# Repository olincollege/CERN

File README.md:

# CERN
ENGR 2110 Final Project: Centripetal Electronic Robotic Navigator (CERN)

#### Final Project by Ari Bobesh (Electrical), Venkadesh Eswaranandam (Electrical), Angela Huang (Mechancial), Sohum Kothavade (Mechanical), and Kevin Lie-Atjam (Firmware/Software)

Welcome to the Centripetal Electronic Robotic Navigator (CERN) project! In this repository, we embark on our exciting journey to build our own version of a Sphero-like robot—a small, spherical robot capable of dynamic movements and engaging interactions. Our goal was to create a Sphero-like robot with inductive charging, a custom PCB, modular and elegant design, and coherent software to control the robot.

## Dependencies and Repository Overview
This software runs on both C++ and Python. Our C++ infrastructure includes firmware for an ESP32 that can run the robot's control algorithms to drive the robot. The Python infrasture include code that is required to connect to the ESP32 over Bluetooth serial to control the robot.

## Repository Structure
The repository has a set of 4 folders which each have important information regarding the items inside of the repository

### app_interface
`app_interface` contains the Python script file required to run our control interface for our robots

### kicad
`kicad` contains a set of schematics and PCB board designs utilized in our project. Inside this folder, the `kicad.kicad_sch` file contains the transmitting circuit for the inductive charging base station. `robot.kicad_sch` and `robot.kicad_pcb` contain the circuit and PCB respectively for the receiving end of the charging circuit and the control circuitry placed inside our robot.

### motor_communicate
`motor_communicate` contains the C++ firmware required to run the robot.

### SymFoot
`SymFoot` contains footprints and symbols for our schematic with unique components not readily available in KiCAD.

### Library installation and Dependencies
To run the software, you will need the following:
* A Unix/Linux Operating System
* A Python Environment (Ex. Anaconda)
* PySerial
* Pygame
* PyBluez

To install the all of the necessary libraries, we recommend doing the following:
* Ensure that you're running a version of Python that is 3.9 or above
* Open a bash terminal on your machine
* Once it loads, I recommend creating a new Anaconda environment. This can be done by doing the following
```
conda create --name <Environment Name> python=3.9
```
Where you may name your environment whatever you would like
* Be patient and make sure that you type y to create your environment after a dialog box appears
* After the environment has been created, run the following command
```
conda activate <Environment Name>
```
To activate your Anaconda environment
* You're now ready to install the libraries to use this repository. Ensure that your file directory is at the root of this repository. By typing `ls` in the repository directory, you should see a file called `requirements.txt`. Finally, you can run the following

```
pip install -r requirements.txt
```
* Be patient and wait for the libraries to finish installing

## Robot Information
We built a set of 3 CERN Robots. The connection information and motor pinouts have been provided

| Name | MAC Address | Drive Pins | Turn Pins |
| ------- | ----- | ----- | ----- |
| Stubby | 78:21:84:B9:0A:1E | A1A: 33<br /> A1B: 32<br /> B1A: 2<br /> B1B: 23<br /> Sleep: 25| A1A: 12<br /> A1B: 14<br /> B1A: 26<br /> B1B: 27<br /> Sleep: 13|
| Girthy | E0:5A:1B:E4:66:56 | A1A: 26<br /> A1B: 27<br /> B1A: 14<br /> B1B: 12<br /> Sleep: 13| A1A: 2<br /> A1B: 23<br /> B1A: 32<br /> B1B: 33<br /> Sleep: 25
| Kirby | E0:5A:1B:E4:9D:D6 | A1A: 32<br /> A1B: 33<br /> B1A: 2<br /> B1B: 23<br /> Sleep: 25| A1A: 12<br /> A1B: 14<br /> B1A: 27<br /> B1B: 26<br /> Sleep: 13

## Connecting To The Robot

These steps work best with Linux based systems

Firstly, make sure that the robot you want to connect to is on. Next, you'll want to connect to the robot by Bluetooth using the systems settings to connect to your robot. You will briefly connect to the robot, but you will then disconnect to the robot. This doesn't mean that you've lost connection, but this only means that you've placed the connection to the robot as a familiar device. Next, you're going to want to run friendly_control.py under the app_interface folder which can be executed by using the following command in a bash terminal: `python friendly_control.py` which will then ask you what device you would like to connect to. You may also open the Python script in a code editor and run the code manually. Once you run the code, it will then ask you to enter your password to because the controls will enter in root. This is because the following code is ran `sudo rfcomm bind <PORT NUMBER> <MAC ADDRESS>` which is when a radio frequency communication port will be established by your computer and robot to the Bluetooth MAC address of your robot. This is important since data is sent over serial for bluetooth. This then opens up a Pygame experience which should allow you obtain live data of the robot, control the lights of the robot, and control the robot using the WASD keys. Once you've finished driving the robot, you may close the Pygame interface, and the following command is ran: `sudo rfcomm release <PORT NUMBER>` which is when the communication port established will be dissolved, and the robot can then be reconnected or connected to another client.

If you have trouble connecting to the robot, typically running `sudo rfcomm release <PORT NUMBER>` to ensure that there doesn't exist a port that already exists that the robot tries to talk to on your computer to is typically recommended.

If you have any questions about any aspect about our project, please feel free to reach out to any of us: Ari Bobesh (abobesh@olin.edu), Kevin Lie-Atjam (klieatjam@olin.edu), Venkadesh Eswaranandam (veswaranandam@olin.edu), Sohum Kothavade (skothavade@olin.edu), and Angela Huang (ahuang3@olin.edu)

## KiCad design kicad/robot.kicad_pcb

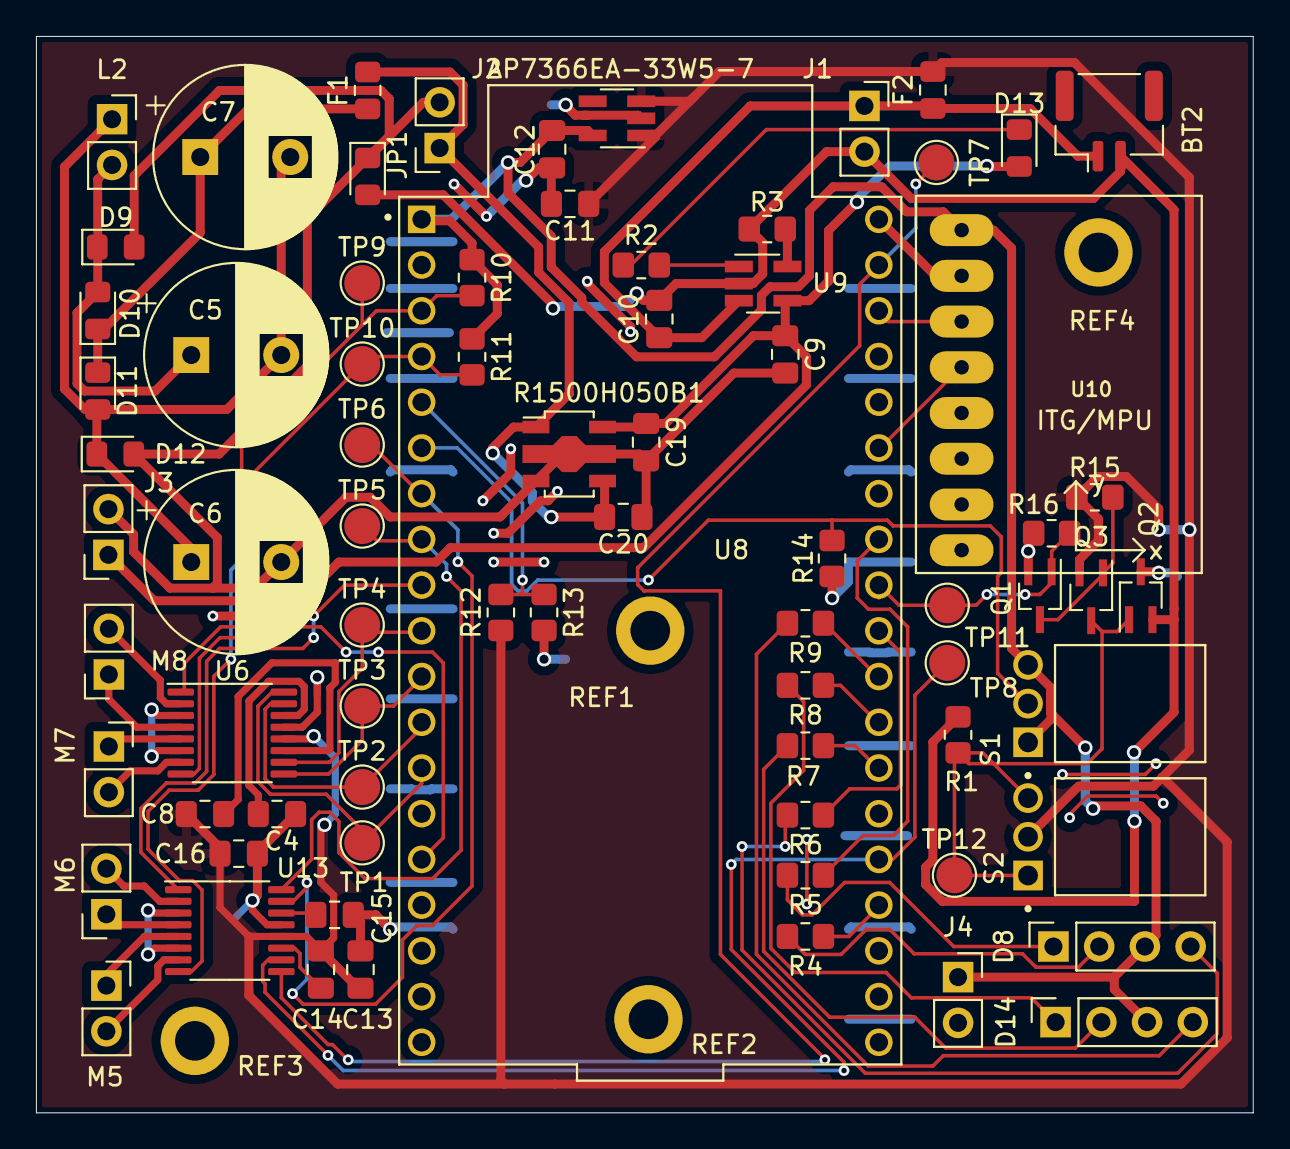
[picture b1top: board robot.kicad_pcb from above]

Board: 2 copper layers, 67.6 x 59.8 mm, 79 parts (0 on the bottom side), 57 nets.

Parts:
AP7366EA-33W5-7: SOT-23-5_HandSoldering
BT2: 1S 3000mAh; JST_GH_BM02B-GHS-TBT_1x02-1MP_P1.25mm_Vertical
C4, C15: 2.2uF,6.3V; C_0805_2012Metric_Pad1.18x1.45mm_HandSolder
C5: C; CP_Radial_D10.0mm_P5.00mm
C6, C7: 1mF; CP_Radial_D10.0mm_P5.00mm
C8, C14: 0.01uF,16V; C_0805_2012Metric_Pad1.18x1.45mm_HandSolder
C9, C10: 4.7uF; C_0805_2012Metric_Pad1.18x1.45mm_HandSolder
C11, C12: 1uF; C_0805_2012Metric_Pad1.18x1.45mm_HandSolder
C13, C16, C19: 10uF; C_0805_2012Metric_Pad1.18x1.45mm_HandSolder
C20: 0.47uF; C_0805_2012Metric_Pad1.18x1.45mm_HandSolder
D8, D14: LED_RGBA; PinSocket_1x04_P2.54mm_Vertical
D9, D10, D11, D12: D; D_0805_2012Metric_Pad1.15x1.40mm_HandSolder
D13: LED; LED_0805_2012Metric_Pad1.15x1.40mm_HandSolder
F1, F2: Fuse; Fuse_0805_2012Metric_Pad1.15x1.40mm_HandSolder
J1, J2, J3, J4: Adafruit Coil Jumper; PinSocket_1x02_P2.54mm_Vertical
JP1: SolderJumper_2_Open; D_0805_2012Metric_Pad1.15x1.40mm_HandSolder
L2: L; PinSocket_1x02_P2.54mm_Vertical
M5, M6, M7, M8: Motor_DC; PinSocket_1x02_P2.54mm_Vertical
Q1, Q2: NMOS; SOT-323_SC-70_Handsoldering
Q3: PMOS; SOT-323_SC-70_Handsoldering
R1, R10, R11, R12, R13, R14, R15, R16: 10k; R_0805_2012Metric_Pad1.20x1.40mm_HandSolder
R2: 150; R_0805_2012Metric_Pad1.20x1.40mm_HandSolder
R3: 2k; R_0805_2012Metric_Pad1.20x1.40mm_HandSolder
R4, R5, R7, R8: 5; R_0805_2012Metric_Pad1.20x1.40mm_HandSolder
R6, R9: 65; R_0805_2012Metric_Pad1.20x1.40mm_HandSolder
R1500H050B1: SOT-89-5
REF1, REF2, REF3, REF4: MountingHole_2.2mm_M2_DIN965_Pad
S1, S2: TM1000Q; SW_TM1000Q
TP1, TP2, TP3, TP4, TP5, TP6, TP7, TP8, TP9, TP10, TP11, TP12: TestPoint; TestPoint_Pad_D2.0mm
U6, U13: DRV8833PW; TSSOP-16_4.4x5mm_P0.65mm
U8: ESP32-DEVKITC; MODULE_ESP32-DEVKITC
U9: MCP73831-2-OT; SOT-23-5_HandSoldering
U10: GY-521

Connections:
/Temporary/Controller/3V3: AP7366EA-33W5-7.5 (OUT), C12.1, D8.3 (A), D14.3 (A), J4.1, R10.1, R11.1, S1.1, S1.3, U8.1 (3V3), U10.VCC
/Temporary/Controller/GND: AP7366EA-33W5-7.2 (GND), C4.1, C11.1, C12.2, C13.1, C15.1, C16.1, J4.2, Q1.2 (S), Q2.3 (D), R13.2, R14.2, R16.2, U6.3 (AISEN), U6.6 (BISEN), U6.13 (GND), U8.38 (GND3), U10.GND, U13.3 (AISEN), U13.6 (BISEN), U13.13 (GND)
/Temporary/Controller/MOSTRIG: Q1.1 (G), R16.1, TP11.1, U8.30 (IO18)
/Temporary/Controller/SCL: U8.36 (IO22), U10.SCL
/Temporary/Controller/SDA: U8.33 (IO21), U10.SDA
/Temporary/Controller/VBAT: AP7366EA-33W5-7.1 (IN), AP7366EA-33W5-7.3 (EN), C8.2, C11.2, C13.2, C14.2, C16.2, F2.2, Q3.2 (S), R12.1, R15.1, S2.2, U6.12 (VM), U13.12 (VM)
unnamed: BT2.1 (+), C10.1, F2.1, J1.1, U9.3 (V_{BAT})
unnamed: BT2.2 (-), C10.2, J1.2, JP1.2 (B), Q2.2 (S), R1.2, R3.2, U9.2 (V_{SS})
unnamed: D8.2 (BK), R4.2
unnamed: D8.1 (GK), R5.2
unnamed: D8.4 (RK), R6.2
unnamed: C5.1, D9.1 (K), D10.2 (A), L2.2
unnamed: C7.1, D10.1 (K), D11.1 (K), F1.1
unnamed: C5.2, C6.1, C7.2, D11.2 (A), D12.1 (K), L2.1
unnamed: C6.2, C9.2, C19.2, C20.2, D9.2 (A), D12.2 (A), J2.2, J3.2, JP1.1 (A), R1500H050B1.2 (GND), R1500H050B1.3 (GND)
unnamed: C9.1, C19.1, D13.2 (A), J3.1, R1500H050B1.5 (Vout), U9.4 (V_{DD})
unnamed: D13.1 (K), R2.1
unnamed: D14.2 (BK), R7.2
unnamed: D14.1 (GK), R8.2
unnamed: D14.4 (RK), R9.2
unnamed: C20.1, F1.2, J2.1, R1500H050B1.1 (Vdd), R1500H050B1.4 (CE)
unnamed: M5.1 (+), U13.5 (BOUT2)
unnamed: M5.2 (-), U13.7 (BOUT1)
unnamed: M6.1 (+), U13.4 (AOUT2)
unnamed: M6.2 (-), U13.2 (AOUT1)
unnamed: M7.1 (+), U6.5 (BOUT2)
unnamed: M7.2 (-), U6.7 (BOUT1)
unnamed: M8.1 (+), U6.4 (AOUT2)
unnamed: M8.2 (-), U6.2 (AOUT1)
unnamed: Q1.3 (D), Q3.1 (G), R15.2
unnamed: Q2.1 (G), Q3.3 (D), R1.1, S2.1, S2.3, TP12.1
unnamed: TP1.1, U6.16 (AIN1), U8.13 (IO12)
unnamed: TP2.1, U6.15 (AIN2), U8.12 (IO14)
unnamed: TP3.1, U6.9 (BIN1), U8.11 (IO27)
unnamed: TP4.1, U6.10 (BIN2), U8.10 (IO26)
unnamed: C8.1, U6.11 (VCP)
unnamed: C4.2, U6.14 (VINT)
unnamed: R10.2, TP9.1, U6.8 (nFAULT), U8.3 (SENSOR_VP)
unnamed: U6.1 (nSLEEP), U8.15 (IO13)
unnamed: R7.1, U8.26 (IO4)
unnamed: R6.1, U8.29 (IO5)
unnamed: R4.1, U8.23 (IO15)
unnamed: R8.1, U8.27 (IO16)
unnamed: R9.1, U8.28 (IO17)
unnamed: R5.1, U8.31 (IO19)
unnamed: R12.2, R13.1, U8.5 (IO34)
unnamed: R14.1, S1.2, U8.6 (IO35)
unnamed: R3.1, U9.5 (PROG)
unnamed: R2.2, U9.1 (STAT)
unnamed: TP5.1, U8.8 (IO33), U13.16 (AIN1)
unnamed: TP6.1, U8.7 (IO32), U13.15 (AIN2)
unnamed: TP7.1, U8.37 (IO23), U13.9 (BIN1)
unnamed: TP8.1, U8.24 (IO2), U13.10 (BIN2)
unnamed: C14.1, U13.11 (VCP)
unnamed: C15.2, U13.14 (VINT)
unnamed: R11.2, TP10.1, U8.4 (SENSOR_VN), U13.8 (nFAULT)
unnamed: U8.9 (IO25), U13.1 (nSLEEP)

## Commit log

2023-10-21 Add induction charging circuit
2023-10-21 Fix transistors on charge management
2023-10-22 Add pulldown resistors
2023-10-22 Create subcircuit sheets
2023-10-22 Subdivide circuits into hierarchical sheets
2023-10-23 Add inverter driver
2023-10-23 Add robot schematic
2023-10-23 Add SymFoots
2023-10-24 Finish Robot Schematic
2023-10-24 Add capacitors
2023-10-25 Add all symbols and values
2023-10-25 Fix footprints
2023-10-26 Add board layout
2023-10-26 Start adding PCB traces
2023-10-26 So many DRC errors
2023-10-26 Add new 3.3V regulator
2023-10-27 Add tilt switch
2023-10-27 First PCB Layout complete
2023-10-27 Add mounting holes
2023-10-29 Fix banned pins on ESP32
2023-10-29 Republish PCB footprint
2023-10-29 Make schematic pretty
2023-10-29 Cleaned up ground traces
2023-10-31 Fix MOSFET footprint pinout
2023-11-01 Change battery connector
2023-11-01 Upload code for sprint 1
2023-11-04 Final PCB
2023-11-06 Successfully implemented basic serial controls
2023-11-16 Pushing bluetooth control code
2023-11-16 Demo code for Sprint 2 review
2023-11-27 Comments, Comments, and more Comments
2023-12-03 Added slowdown sequence
2023-12-03 Add LED control
2023-12-04 Fix small integration issues for LEDs
2023-12-05 Code instantiated for x-axis correction
2023-12-06 Changed visual interface
2023-12-06 Add remote and idle kill and uv startup protection
2023-12-07 Add kirby code
2023-12-07 Cleaning up repository structure
2023-12-15 Update induction charging schematic
